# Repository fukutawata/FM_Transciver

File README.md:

# FM_Transciver
very small fm transciver

# Built with
Kicad (ver. 6.0.9)
https://www.kicad.org

freerouting (ver.1.6.2)
https://github.com/freerouting/freerouting

supplier:JLCPCB
https://jlcpcb.com

# IC Parts
- BA1404(Datasheet: https://www.alldatasheet.jp/datasheet-pdf/pdf/35925/ROHM/BA1404.html)

- RTC6215S(Datasheet: http://aitendo3.sakura.ne.jp/aitendo_data/product_img/ic/radio/RTC6215/T-ST-6215N-DST-001-aitendo.pdf)
(This datasheet is RTC6215N. The internal structure of RTC6215N is the same as RTC6215N, but external structure is SSOP-16.(pitch:0.65mm)

# Overview
- overall schematic

- wiring diagram of the circuit

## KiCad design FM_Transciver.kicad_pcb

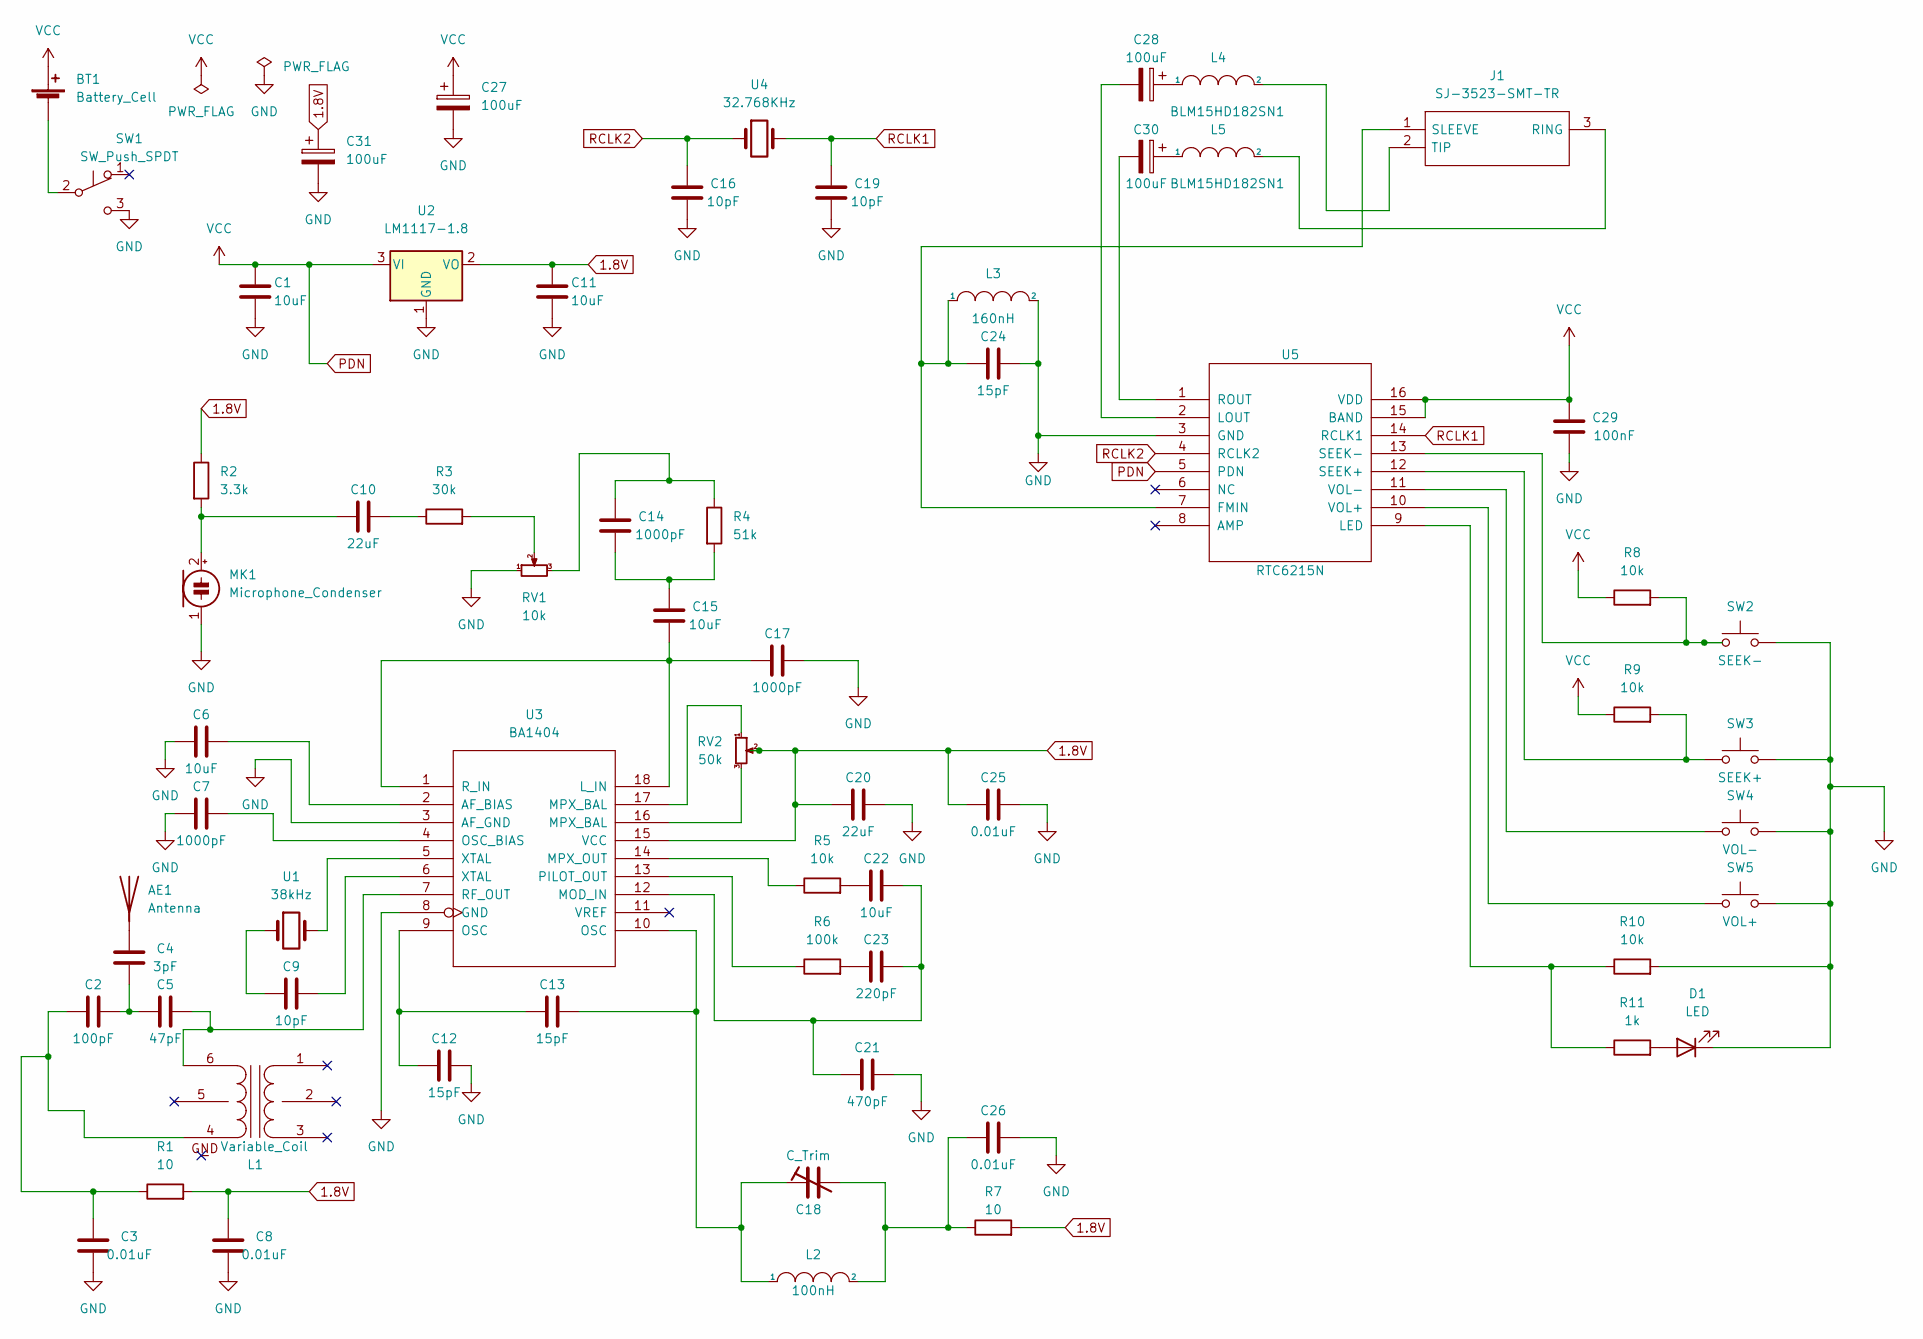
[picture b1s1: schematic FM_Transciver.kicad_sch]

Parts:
AE1: Antenna; PinSocket_1x01_P2.54mm_Vertical
BT1: Battery_Cell; PinSocket_1x02_P2.54mm_Vertical
C1, C6, C11, C15, C22: 10uF; C_0603_1608Metric_Pad1.08x0.95mm_HandSolder
C2: 100pF; C_0603_1608Metric_Pad1.08x0.95mm_HandSolder
C3, C8, C25, C26: 0.01uF; C_0603_1608Metric_Pad1.08x0.95mm_HandSolder
C4: 3pF; C_0603_1608Metric_Pad1.08x0.95mm_HandSolder
C5: 47pF; C_0603_1608Metric_Pad1.08x0.95mm_HandSolder
C7, C14, C17: 1000pF; C_0603_1608Metric_Pad1.08x0.95mm_HandSolder
C9, C16, C19: 10pF; C_0603_1608Metric_Pad1.08x0.95mm_HandSolder
C10, C20: 22uF; C_0603_1608Metric_Pad1.08x0.95mm_HandSolder
C12, C13, C24: 15pF; C_0603_1608Metric_Pad1.08x0.95mm_HandSolder
C18: C_Trim; Trimmer_Cap_TZ03
C21: 470pF; C_0603_1608Metric_Pad1.08x0.95mm_HandSolder
C23: 220pF; C_0603_1608Metric_Pad1.08x0.95mm_HandSolder
C27, C28, C30, C31: 100uF; CP_Radial_D5.0mm_P2.50mm
C29: 100nF; C_0603_1608Metric_Pad1.08x0.95mm_HandSolder
D1: LED; LED_0603_1608Metric_Pad1.05x0.95mm_HandSolder
J1: SJ-3523-SMT-TR; SJ3523SMTTR; Mouser Part Number 490-SJ-3523-SMT-TR
L1: Variable_Coil; VariableCoils-5CCEG
L2: 100nH; L_01005_0402Metric_Pad0.57x0.30mm_HandSolder
L3: 160nH; L_01005_0402Metric_Pad0.57x0.30mm_HandSolder
L4, L5: BLM15HD182SN1; L_01005_0402Metric_Pad0.57x0.30mm_HandSolder
MK1: Microphone_Condenser; CP_Radial_D5.0mm_P2.50mm
R1, R7: 10; R_0603_1608Metric_Pad0.98x0.95mm_HandSolder
R2: 3.3k; R_0603_1608Metric_Pad0.98x0.95mm_HandSolder
R3: 30k; R_0603_1608Metric_Pad0.98x0.95mm_HandSolder
R4: 51k; R_0603_1608Metric_Pad0.98x0.95mm_HandSolder
R5, R8, R9, R10: 10k; R_0603_1608Metric_Pad0.98x0.95mm_HandSolder
R6: 100k; R_0603_1608Metric_Pad0.98x0.95mm_HandSolder
R11: 1k; R_0603_1608Metric_Pad0.98x0.95mm_HandSolder
RV1: 10k; VariableResister
RV2: 50k; VariableResister
SW1: SW_Push_SPDT; slideSwitch1
SW2: SEEK-; tactswitch1
SW3: SEEK+; tactswitch1
SW4: VOL-; tactswitch1
SW5: VOL+; tactswitch1
U1: 38kHz; Crystal_Round_D2.0mm_Vertical
U2: LM1117-1.8; SOT-223-3_TabPin2
U3: BA1404; DIP-18_W7.62mm
U4: 32.768KHz; Crystal_SMD_3215-2Pin_3.2x1.5mm
U5: RTC6215N; RTC6215S

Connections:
1.8V: C8.1, C11.1, C20.2, C25.2, C31.1, R1.2, R2.1, R7.2, RV2.2, U2.2 (VO), U3.15 (VCC)
GND: C1.2, C3.2, C6.2, C7.2, C8.2, C11.2, C12.1, C16.2, C17.1, C19.2, C20.1, C21.1, C24.1, C25.1, C26.1, C27.2, C29.2, C31.2, D1.1 (K), L3.2, MK1.1 (-), R10.2, RV1.1, SW1.3 (C), SW2.2, SW3.2, SW4.2, SW5.2, U2.1 (GND), U3.3 (AF_GND), U3.8 (GND), U5.3 (GND)
unnamed: AE1.1 (A), C4.1
unnamed: BT1.2 (-), SW1.2 (B)
unnamed: C2.1, C4.2, C5.2
unnamed: C2.2, C3.1, L1.4 (SB), R1.1
unnamed: C5.1, L1.6 (SA), U3.7 (RF_OUT)
unnamed: C6.1, U3.2 (AF_BIAS)
unnamed: C7.1, U3.4 (OSC_BIAS)
unnamed: C9.1, U3.6 (XTAL)
unnamed: C9.2, U1.1
unnamed: C10.1, R3.1
unnamed: C10.2, MK1.2 (+), R2.2
unnamed: C12.2, C13.2, U3.9 (OSC)
unnamed: C13.1, C18.1, L2.1, U3.10 (OSC)
unnamed: C14.1, R4.1, RV1.3
unnamed: C14.2, C15.1, R4.2
unnamed: C15.2, C17.2, U3.1 (R_IN), U3.18 (L_IN)
unnamed: C18.2, C26.2, L2.2, R7.1
unnamed: C21.2, C22.1, C23.1, U3.12 (MOD_IN)
unnamed: C22.2, R5.2
unnamed: C23.2, R6.2
unnamed: C24.2, J1.1 (SLEEVE), L3.1, U5.7 (FMIN)
unnamed: C28.1, L4.1
unnamed: C28.2, U5.2 (LOUT)
unnamed: C30.1, L5.1
unnamed: C30.2, U5.1 (ROUT)
unnamed: D1.2 (A), R11.2
unnamed: J1.2 (TIP), L4.2
unnamed: J1.3 (RING), L5.2
unnamed: R3.2, RV1.2
unnamed: R5.1, U3.14 (MPX_OUT)
unnamed: R6.1, U3.13 (PILOT_OUT)
unnamed: R8.2, SW2.1, U5.13 (SEEK-)
unnamed: R9.2, SW3.1, U5.12 (SEEK+)
unnamed: R10.1, R11.1, U5.9 (LED)
unnamed: RV2.1, U3.17 (MPX_BAL)
unnamed: RV2.3, U3.16 (MPX_BAL)
unnamed: SW4.1, U5.11 (VOL-)
unnamed: SW5.1, U5.10 (VOL+)
unnamed: U1.2, U3.5 (XTAL)
PDN: BT1.1 (+), C1.1, C27.1, C29.1, R8.1, R9.1, U2.3 (VI), U5.5 (PDN), U5.15 (BAND), U5.16 (VDD)
RCLK1: C19.1, U4.2, U5.14 (RCLK1)
RCLK2: C16.1, U4.1, U5.4 (RCLK2)

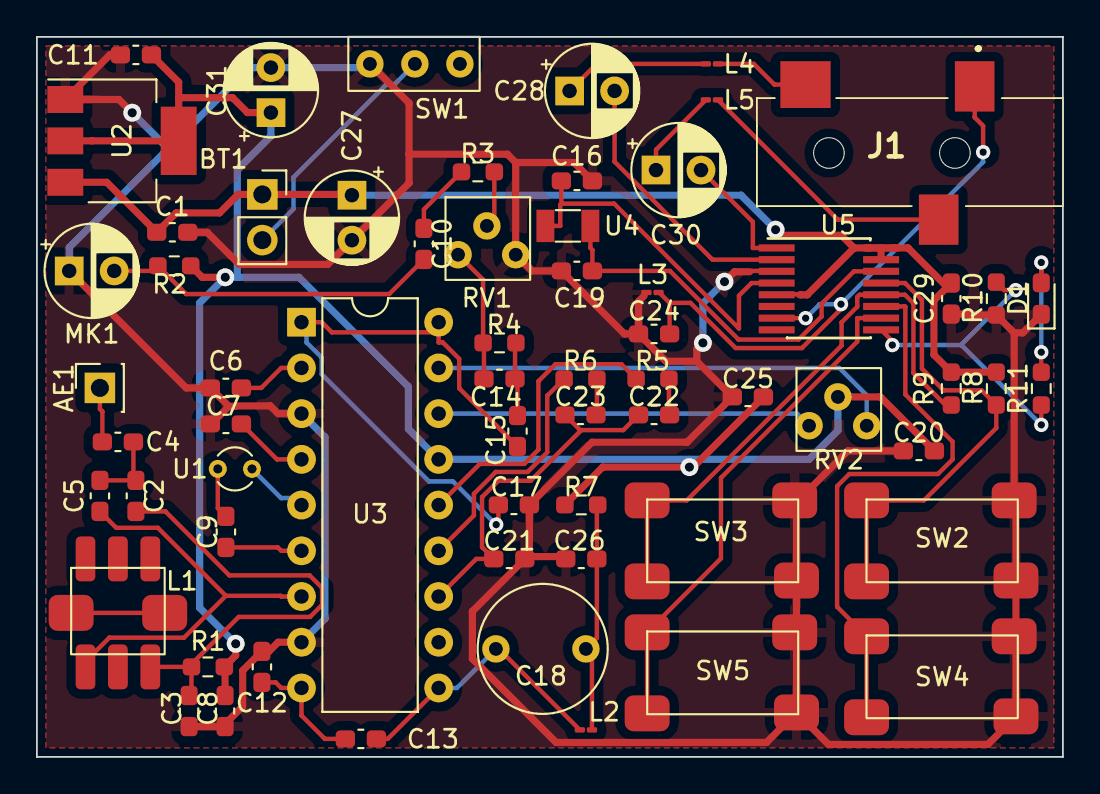
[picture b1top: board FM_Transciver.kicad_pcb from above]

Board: 2 copper layers, 57.0 x 40.0 mm, 64 parts (0 on the bottom side), 44 nets.
